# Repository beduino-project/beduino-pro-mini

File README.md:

Beduino Pro Mini
================

The Beduino Pro Mini is a prototyping board based on the NXP MKW41Z SoC:

* ARM Cortex-M0+ CPU
* 64/128 KB RAM
* 256/512 KB flash
* 2.4 GHz transceiver supporting Bluetooth Low Energy and IEEE 802.15.4
* AES-128 Hardware Accelerator
* True Random Number Generator

In addition to the SoC, the board features the following:

* 2.4 GHz trace antenna
* LDO voltage regulator for 5V supply
* The necessary oscillators and passive components
* Two LEDs (red and green)
* Reset button

The board layout also includes a DIPDAP programmer, which can be
detached from the Beduino Pro Mini (using a fine saw or a dremel tool)
and later reconnected using the usual seven-pin DIPDAP header.
The programmer features the following:

* USB connection
* Flashing and debugging of the MKW41Z using SWD
* Fully supported in OpenOCD
* USB-to-Serial adapter
* Powering of Beduino Pro Mini over USB

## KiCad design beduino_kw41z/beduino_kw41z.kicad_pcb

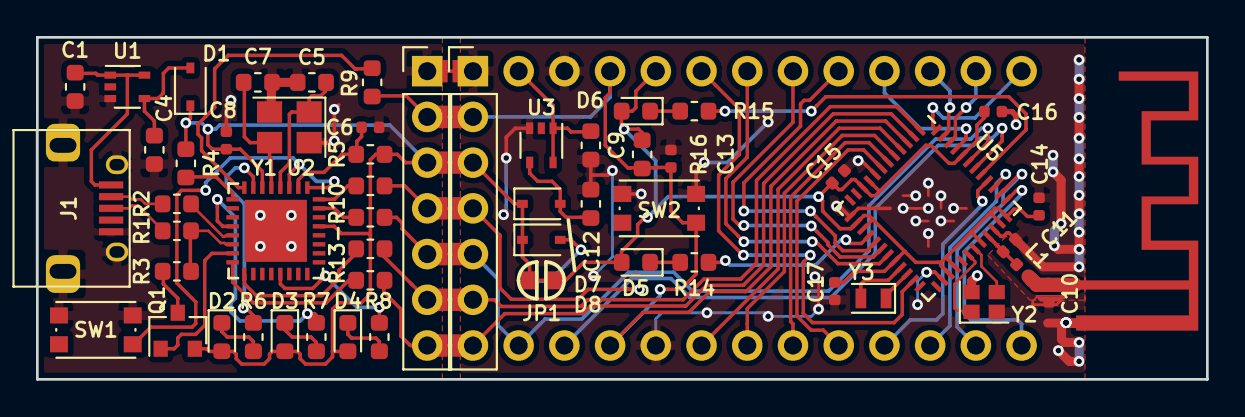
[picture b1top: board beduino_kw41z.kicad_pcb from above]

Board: 2 copper layers, 65.0 x 19.0 mm, 57 parts (1 on the bottom side), 60 nets.

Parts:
ANT1: SWRA117D
BT1: Battery_Cell; Keystone_1058_1x2032-CoinCell
C1, C9: 1u; C_0603_1608Metric
C4, C12: 10u; C_0603_1608Metric
C5, C7: 18p; C_0603_1608Metric
C6, C8, C13, C14, C15, C16, C17: 100n; C_0402_1005Metric
C10, C11: 0.7p; C_0402_1005Metric
D1, D7, D8: BAT60A; D_SOD-323
D2, D5: Red; LED_0603_1608Metric
D3: Yellow; LED_0603_1608Metric
D4, D6: Green; LED_0603_1608Metric
J1: USB_OTG; USB_Micro-B
J2, J3: Conn_01x07; Pin_Header_Straight_1x07_Pitch2.54mm
JP1: Power; SOLDER-JUMPER_1-WAY
L1: 5.1n; L_0402_1005Metric
Q1: Q_PMOS_GSD; SOT-23
R1, R2: 33; R_0603_1608Metric
R3: 1k5; R_0603_1608Metric
R4, R5, R16: 10k; R_0603_1608Metric
R6, R7, R8, R9, R10, R11, R13, R13-R10, R14, R15: 470; R_0603_1608Metric
SW1: SW_Push; SW_SPST_KMR2
SW2: Reset; SW_SPST_KMR2
U1, U3: TC1017; SOT-353_SC-70-5
U2: LPC11U35FHI33-501; QFN-32-1EP_5x5mm_P0.5mm_EP3.45x3.45mm
U4: Module_CONN; Arduino_Mini
U5: MKW41Z; QFN-48-1EP_7x7mm_P0.5mm_EP5.15x5.15mm
Y1: 12MHz; Crystal_SMD_3225-4Pin_3.2x2.5mm
Y2: 32MHz; Crystal_SMD_2016-4Pin_2.0x1.6mm
Y3: 32KHz; Crystal_SMD_2012-2Pin_2.0x1.2mm

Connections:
+3V3: C8.1, C14.1, C15.1, C16.1, C17.1, D1.1, D2.2, D3.2, D4.2, D5.2, D6.2, D7.1, D8.1, J2.3, J3.3, JP1.1, JP1.2, Q1.2, R4.1, R5.2, R16.1, U2.6, U2.29, U4.21, U5.9, U5.10, U5.14, U5.15, U5.20, U5.27, U5.28, U5.32, U5.35, U5.36, U5.44
/DIPDAP/TGT_NRESET: C13.1, J2.2, J3.2, R9.1, R16.2, SW2.2, U4.3, U4.22, U5.3
/DIPDAP/TGT_RX: J2.4, J3.4, R10.1, U4.2, U5.42
/DIPDAP/TGT_SWCLK: J2.7, J3.7, R13.1, U5.2
/DIPDAP/TGT_SWDIO: J2.6, J3.6, R13-R10.1, U5.1
/DIPDAP/TGT_TX: J2.5, J3.5, R11.1, U4.1, U5.43
/KW41Z/A0: U4.17, U5.17
/KW41Z/A1: U4.18, U5.18
/KW41Z/A2: U4.19, U5.19
/KW41Z/A3: U4.20, U5.23
/KW41Z/ANT: C11.1, L1.1, U5.33
/KW41Z/D2: U4.5, U5.4
/KW41Z/D3: U4.6, U5.5
/KW41Z/D4: U4.7, U5.6
/KW41Z/D5: U4.8, U5.7
/KW41Z/D6: U4.9, U5.40
/KW41Z/D9: U4.12, U5.37
/KW41Z/D10: U4.13, U5.48
/KW41Z/LED_Green: R15.1, U5.41
/KW41Z/LED_Red: R14.1, U5.16
/KW41Z/MISO: U4.15, U5.47
/KW41Z/MOSI: U4.14, U5.46
/KW41Z/SCK: U4.16, U5.45
/KW41Z/SCL: U4.11, U5.38
/KW41Z/SDA: U4.10, U5.39
GND: ANT1.2, BT1.2, C1.2, C4.2, C5.2, C6.2, C7.2, C8.2, C9.2, C10.2, C11.2, C12.2, C13.2, C14.2, C15.2, C16.2, C17.2, J1.5, J1.6, J2.1, J3.1, SW1.1, SW2.1, U1.3, U2.33, U3.3, U4.4, U4.23, U5.8, U5.13, U5.26, U5.34, Y1.2, Y1.4, Y2.2, Y2.4
unnamed: ANT1.1, C10.1, L1.2
unnamed: BT1.1, D8.2
unnamed: R2.1, U2.13
unnamed: R1.1, R3.1, U2.14
unnamed: C4.1, D1.2, U1.4
unnamed: C5.1, U2.4, Y1.1
unnamed: C6.1, R5.1, U2.2
unnamed: C7.1, U2.5, Y1.3
unnamed: C12.1, D7.2, U3.4
unnamed: D2.1, R6.1
unnamed: D3.1, R7.1
unnamed: D4.1, R8.1
unnamed: D5.1, R14.2
unnamed: D6.1, R15.2
unnamed: J1.2, R2.2
unnamed: J1.3, R1.2
unnamed: Q1.1, U2.15
unnamed: Q1.3, R3.2
unnamed: R4.2, U2.9
unnamed: R6.2, U2.7
unnamed: R7.2, U2.12
unnamed: R8.2, U2.21
unnamed: R9.2, U2.8
unnamed: R10.2, U2.32
unnamed: R11.2, U2.31
unnamed: R13-R10.2, U2.17
unnamed: R13.2, U2.16
unnamed: SW1.2, U2.1, U2.3
unnamed: U5.21, Y3.2
unnamed: U5.22, Y3.1
unnamed: U5.30, Y2.1
unnamed: U5.31, Y2.3
VBUS: C1.1, J1.1, U1.1, U1.5
VCC: C9.1, U3.1, U3.5, U4.24

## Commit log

2017-12-03 Add gitignore for kicad files
2017-12-03 Add schematic files for the pcb and the created libraries.
2017-12-03 Add antenna libraries and antenna hardware design.
2017-12-04 Add jumper into the power trace.
    This makes it possible to measure the current used by the module.
2017-12-04 Change 32MHz Crystal to a 4 pin type.
2017-12-12 Update schematic for new KiCAD version.
    Also add some components.
2017-12-12 Add initial component placement.
2017-12-12 Add some initial routing ideas.
2017-12-12 Some more PCB design work.
2017-12-16 Small changes in the schematics.
2017-12-16 Finished routing. Needs checking.
2017-12-18 Move some traces to improve the design a bit.
2017-12-21 Small improvements to the PCB design.
2018-01-23 Add panelized pcb
2018-01-26 add BOM with mouser part numbers
2018-01-28 updated to mouser cart 28.01.2018 11:55:35
2018-02-26 Fix board design errors.
    This also migrates the files back to the kicad v4 file format. Otherwise
    everyone would need to build kicad from git.
2018-03-16 Update board design to be kicad v4 compatible again.
2018-03-16 Update multi pcb design to be kicad v4 compatible.
2018-04-17 Add zelflex qr templates.
2018-05-25 add svg for the stencil
2018-05-25 Improve stencil svg
2018-12-09 Update PCB layout.
    The connection between the dipdap and the kw41z-mini is now closed with
    a small trace. If the trace is cut, added smd pads simplify the creation
    of solder jumpers.
2018-12-09 Add script to create a panel from the design.
2018-12-09 Add original schematic and pcb layout for the kw41z-mini.
    Also add pinout diagram for the swd socket.
2018-12-12 Add license informations.
2018-12-12 Remove unused stuff.
2018-12-12 add RIOT app for QA
2018-12-12 cleanup
2018-12-12 add README

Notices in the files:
beduino_kw41z/beduino_kw41z.kicad_pcb:
License: Solderpad Hardware License 2.0
Copyright 2018 Maximilian Luenert
